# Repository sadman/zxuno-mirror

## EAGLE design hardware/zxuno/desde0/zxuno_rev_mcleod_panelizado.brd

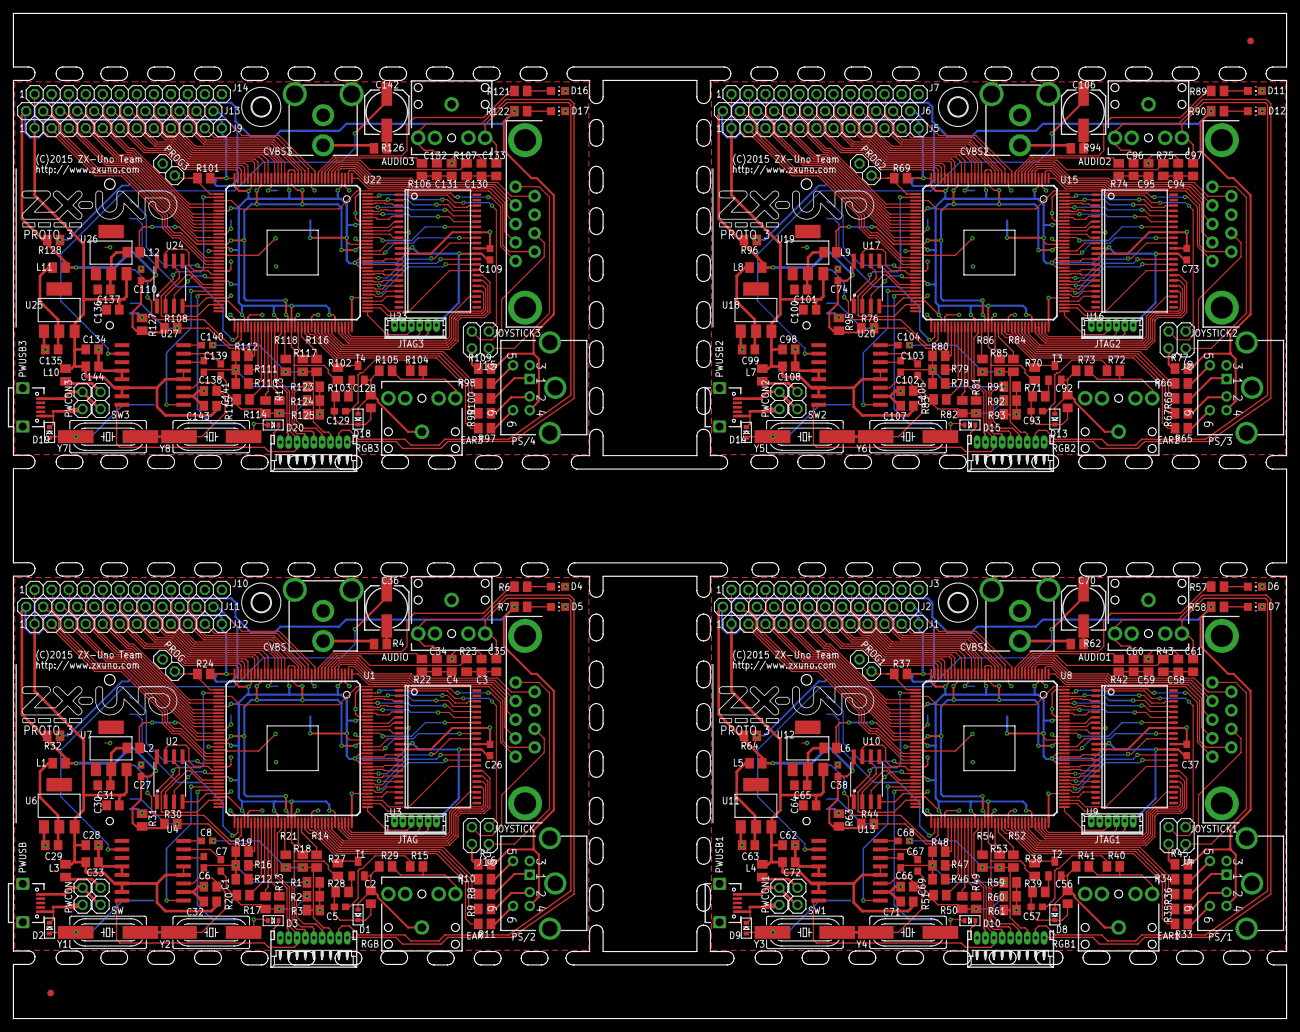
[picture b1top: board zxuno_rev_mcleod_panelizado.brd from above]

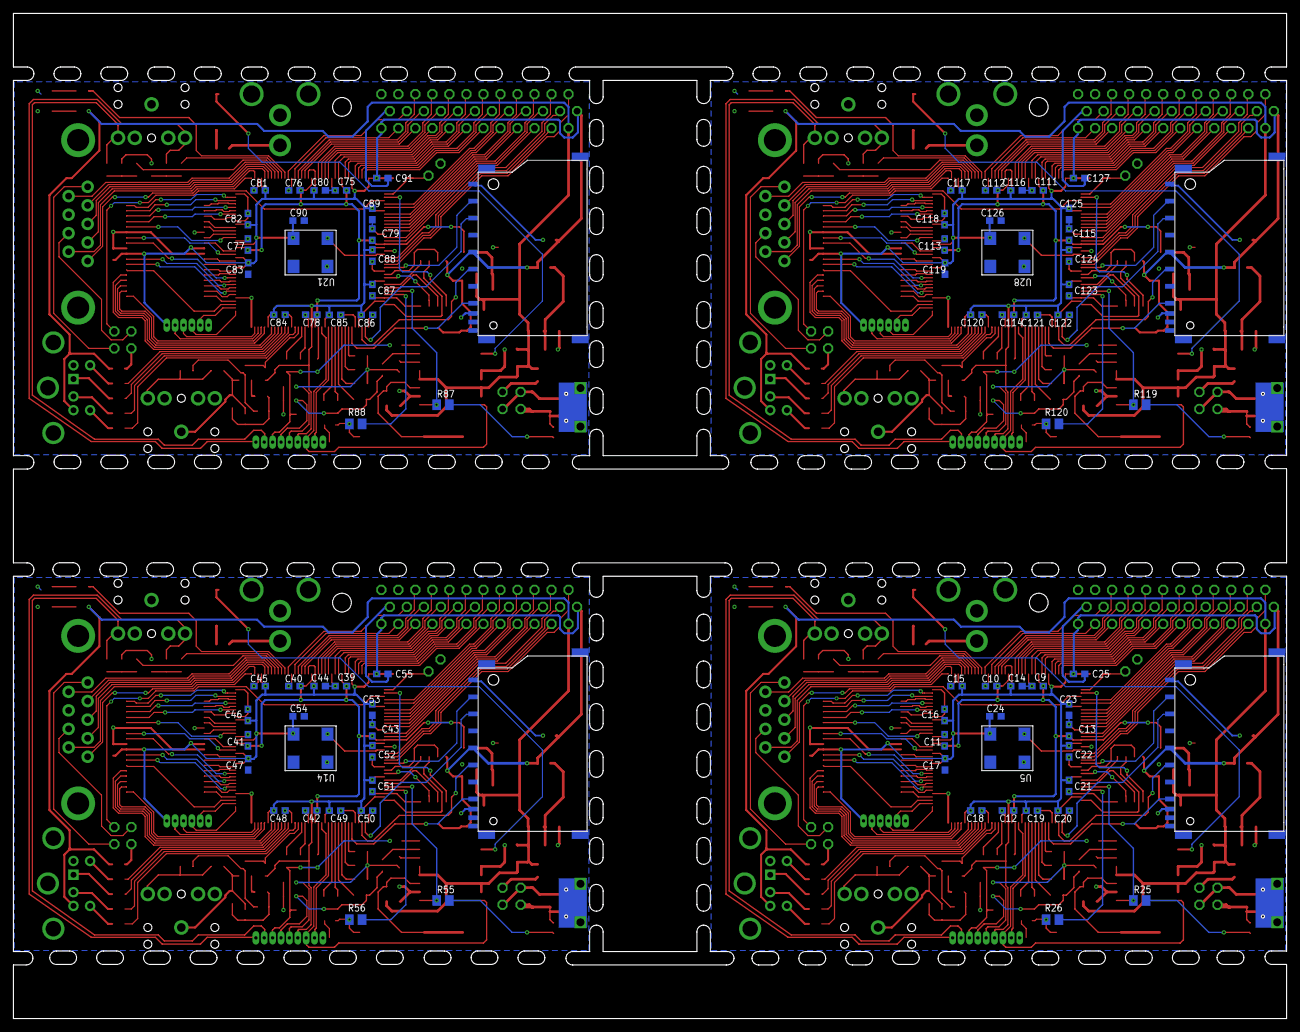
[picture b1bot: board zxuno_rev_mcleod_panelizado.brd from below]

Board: 2 copper layers, 190.0 x 150.0 mm, 414 parts (84 on the bottom side), 572 nets.

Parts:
AUDIO, AUDIO1, AUDIO2, AUDIO3: Audio; AUDIO-JACK
C1, C69, C105, C141: 7.5pF; C0805
C2, C3, C4, C56, C58, C59, C92, C94, C95, C128, C130, C131: 10nF; C0805
C5, C6, C7, C8, C9, C10, C11, C12, C13, C14, C15, C16, C17, C18, C19, C20, C21, C22, C23, C24, C25, C26, C27, C37, C38, C39, C40, C41, C42, C43, C44, C45, C46, C47, C48, C49, C50, C51, C52, C53, C54, C55, C57, C66, C67, C68, C73, C74, C75, C76, C77, C78, C79, C80, C81, C82, C83, C84, C85, C86, C87, C88, C89, C90, C91, C93, C102, C103, C104, C109, C110, C111, C112, C113, C114, C115, C116, C117, C118, C119, C120, C121, C122, C123, C124, C125, C126, C127, C129, C138, C139, C140: 100nF; C0603
C28, C29, C30, C31, C32, C33, C34, C35, C60, C61, C62, C63, C64, C65, C71, C72, C96, C97, C98, C99, C100, C101, C107, C108, C132, C133, C134, C135, C136, C137, C143, C144: 10uF; C0805
C36, C70, C106, C142: 220uF; 153CLV-0605
CVBS, CVBS1, CVBS2, CVBS3: RCA; RCA_JACK_RCJ-04X_-_DUPLICATE_1PRIMARY
D1, D2, D3, D8, D9, D10, D13, D14, D15, D18, D19, D20: SOD-523
D4, D5, D6, D7, D11, D12, D16, D17: CHIP-LED0805
E$1, E$2: FIDUCIAL_1MM
EAR, EAR1, EAR2, EAR3: EAR; AUDIO-JACK
H1, H2, H3, H4: MOUNT-HOLE2.8; 2,8
J1, J2, J3, J5, J6, J7, J9, J10, J11, J12, J13, J14: 1X12
J4, J8, J15, J16: 2X02
JOYSTICK, JOYSTICK1, JOYSTICK2, JOYSTICK3: DB9_MALE
JTAG, JTAG1, JTAG2, JTAG3: JTAG; 53047-06
L1, L2, L3, L4, L5, L6, L7, L8, L9, L10, L11, L12: M0805
PROG, PROG1, PROG2, PROG3: 1X02
PS/1, PS/2, PS/3, PS/4: PS/2 Keyb; DINC/MIN_TM/6_1PRIMARY
PWCON, PWCON1, PWCON2, PWCON3: 1X02
PWUSB, PWUSB1, PWUSB2, PWUSB3: MICROUSB; MICRO_USB_1PRIMARY
R1, R2, R3, R4, R59, R60, R61, R62, R91, R92, R93, R94, R123, R124, R125, R126: 75; M0805
R5, R6, R7, R8, R9, R10, R11, R12, R13, R14, R15, R33, R34, R35, R36, R40, R45, R46, R49, R52, R57, R58, R65, R66, R67, R68, R72, R77, R78, R81, R84, R89, R90, R97, R98, R99, R100, R104, R109, R110, R113, R116, R121, R122: 510; M0805
R16, R17, R18, R47, R50, R53, R79, R82, R85, R111, R114, R117: 1K; M0805
R19, R20, R21, R22, R23, R24, R37, R42, R43, R48, R51, R54, R69, R74, R75, R80, R83, R86, R101, R106, R107, R112, R115, R118: 2K; M0805
R25, R26, R27, R28, R29, R30, R31, R32, R38, R39, R41, R44, R55, R56, R63, R64, R70, R71, R73, R76, R87, R88, R95, R96, R102, R103, R105, R108, R119, R120, R127, R128: 10K; M0805
RGB, RGB1, RGB2, RGB3: RGB; 53048-09
SDCARD, SDCARD1, SDCARD2, SDCARD3: SDCMF-10915W010
SW, SW1, SW2, SW3: 1X02
T1, T2, T3, T4: BC846; SOT23
U1, U8, U15, U22: 6SLX9TQG144; TQ144
U2, U10, U17, U24: FLASH-SPI-25XXSMD1; SO08-EIAJ
U3, U9, U16, U23: TSOP44-II
U4, U13, U20, U27: AD724; SO16W
U5, U14, U21, U28: 50MHz; SM/OSC_1PRIMARY
U6, U11, U18, U25: 3.3V; SOT223
U7, U12, U19, U26: 1.2V; SOT223
Y1, Y3, Y5, Y7: 3.58M; HC49UP
Y2, Y4, Y6, Y8: 4.43M; HC49UP

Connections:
1.2V: C9.2, C10.2, C11.2, C12.2, C13.2, L2.2, U1.P19, U1.P28, U1.P52, U1.P89, U1.P128
1.2V1: C39.2, C40.2, C41.2, C42.2, C43.2, L6.2, U8.P19, U8.P28, U8.P52, U8.P89, U8.P128
1.2V2: C75.2, C76.2, C77.2, C78.2, C79.2, L9.2, U15.P19, U15.P28, U15.P52, U15.P89, U15.P128
1.2V3: C111.2, C112.2, C113.2, C114.2, C115.2, L12.2, U22.P19, U22.P28, U22.P52, U22.P89, U22.P128
3.3V: C14.2, C15.2, C16.2, C17.2, C18.2, C19.2, C20.2, C21.2, C22.2, C23.2, C24.2, C25.2, C26.1, C27.2, J11.1, J12.12, JTAG.1, L1.2, R24.2, R27.2, R30.1, R31.2, R32.2, RGB.4, SDCARD.4, U1.P4, U1.P18, U1.P20, U1.P31, U1.P36, U1.P42, U1.P53, U1.P63, U1.P69, U1.P76, U1.P86, U1.P90, U1.P103, U1.P122, U1.P125, U1.P129, U1.P135, U2.8, U3.11, U3.33, U5.4
3.3V1: C37.1, C38.2, C44.2, C45.2, C46.2, C47.2, C48.2, C49.2, C50.2, C51.2, C52.2, C53.2, C54.2, C55.2, J1.12, J2.1, JTAG1.1, L5.2, R37.2, R38.2, R44.1, R63.2, R64.2, RGB1.4, SDCARD1.4, U8.P4, U8.P18, U8.P20, U8.P31, U8.P36, U8.P42, U8.P53, U8.P63, U8.P69, U8.P76, U8.P86, U8.P90, U8.P103, U8.P122, U8.P125, U8.P129, U8.P135, U9.11, U9.33, U10.8, U14.4
3.3V2: C73.1, C74.2, C80.2, C81.2, C82.2, C83.2, C84.2, C85.2, C86.2, C87.2, C88.2, C89.2, C90.2, C91.2, J5.12, J6.1, JTAG2.1, L8.2, R69.2, R70.2, R76.1, R95.2, R96.2, RGB2.4, SDCARD2.4, U15.P4, U15.P18, U15.P20, U15.P31, U15.P36, U15.P42, U15.P53, U15.P63, U15.P69, U15.P76, U15.P86, U15.P90, U15.P103, U15.P122, U15.P125, U15.P129, U15.P135, U16.11, U16.33, U17.8, U21.4
3.3V3: C109.1, C110.2, C116.2, C117.2, C118.2, C119.2, C120.2, C121.2, C122.2, C123.2, C124.2, C125.2, C126.2, C127.2, J9.12, J13.1, JTAG3.1, L11.2, R101.2, R102.2, R108.1, R127.2, R128.2, RGB3.4, SDCARD3.4, U22.P4, U22.P18, U22.P20, U22.P31, U22.P36, U22.P42, U22.P53, U22.P63, U22.P69, U22.P76, U22.P86, U22.P90, U22.P103, U22.P122, U22.P125, U22.P129, U22.P135, U23.11, U23.33, U24.8, U28.4
5V: C28.1, C30.1, C32.2, C33.2, J12.1, L3.2, PS/2.4, R5.1, R7.2, U4.4, U4.5, U4.14, U4.15, U6.3, U7.3
5V1: C62.1, C64.1, C71.2, C72.2, J1.1, L4.2, PS/1.4, R45.1, R58.2, U11.3, U12.3, U13.4, U13.5, U13.14, U13.15
5V2: C98.1, C100.1, C107.2, C108.2, J5.1, L7.2, PS/3.4, R77.1, R90.2, U18.3, U19.3, U20.4, U20.5, U20.14, U20.15
5V3: C134.1, C136.1, C143.2, C144.2, J9.1, L10.2, PS/4.4, R109.1, R122.2, U25.3, U26.3, U27.4, U27.5, U27.14, U27.15
AUDIO_LEFT: R22.2, U1.P10
AUDIO_LEFT1: R42.2, U8.P10
AUDIO_LEFT2: R74.2, U15.P10
AUDIO_LEFT3: R106.2, U22.P10
AUDIO_RIGHT: R23.2, U1.P9
AUDIO_RIGHT1: R43.2, U8.P9
AUDIO_RIGHT2: R75.2, U15.P9
AUDIO_RIGHT3: R107.2, U22.P9
B: C6.2, R1.1, R12.1, R16.1, R19.1, RGB.5
B0: R19.2, U1.P79
B1: R16.2, U1.P80
B2: R12.2, U1.P81
B3: R48.2, U8.P79
B4: R47.2, U8.P80
B5: R46.2, U8.P81
B6: C66.2, R46.1, R47.1, R48.1, R59.1, RGB1.5
B7: R80.2, U15.P79
B8: R79.2, U15.P80
B9: R78.2, U15.P81
B10: C102.2, R78.1, R79.1, R80.1, R91.1, RGB2.5
B11: R112.2, U22.P79
B12: R111.2, U22.P80
B13: R110.2, U22.P81
B14: C138.2, R110.1, R111.1, R112.1, R123.1, RGB3.5
CLK: U1.P55, U5.3
CLK1: U8.P55, U14.3
CLK2: U15.P55, U21.3
CLK3: U22.P55, U28.3
CSYNC: RGB.3, U1.P87, U4.16
CSYNC1: RGB1.3, U8.P87, U13.16
CSYNC2: RGB2.3, U15.P87, U20.16
CSYNC3: RGB3.3, U22.P87, U27.16
EAR: R27.1, T1.3, U1.P94
EAR1: R38.1, T2.3, U8.P94
EAR2: R70.1, T3.3, U15.P94
EAR3: R102.1, T4.3, U22.P94
EXT1: J1.2, U8.P57
EXT2: J2.2, U8.P56
EXT3: J3.2, U8.P51
EXT4: J1.3, U8.P50
EXT5: J2.3, U8.P48
EXT6: J10.1, U1.P58
EXT7: J12.2, U1.P57
EXT8: J11.2, U1.P56
EXT9: J10.2, U1.P51
EXT10: J12.3, U1.P50
EXT11: J11.3, U1.P48
EXT12: J10.3, U1.P47
EXT13: J12.4, U1.P46
EXT14: J11.4, U1.P45
EXT15: J10.4, U1.P44
EXT16: J12.5, U1.P43
EXT17: J11.5, U1.P41
EXT18: J10.5, U1.P40
EXT19: J12.6, U1.P35
EXT20: J11.6, U1.P34
EXT21: J10.6, U1.P33
EXT22: J12.7, U1.P32
EXT23: J11.7, U1.P30
EXT24: J10.7, U1.P29
EXT25: J12.8, U1.P27
EXT26: J11.8, U1.P26
EXT27: J10.8, U1.P24
EXT28: J12.9, U1.P23
EXT29: J11.9, U1.P22
EXT30: J10.9, U1.P21
EXT31: J12.10, U1.P17
EXT32: J11.10, U1.P16
EXT33: J10.10, U1.P15
EXT34: J12.11, U1.P14
EXT35: J11.11, U1.P12
EXT36: J3.3, U8.P47
EXT37: J1.4, U8.P46
EXT38: J2.4, U8.P45
EXT39: J3.4, U8.P44
EXT40: J1.5, U8.P43
EXT41: J2.5, U8.P41
EXT42: J3.5, U8.P40
EXT43: J1.6, U8.P35
EXT44: J2.6, U8.P34
EXT45: J3.6, U8.P33
EXT46: J1.7, U8.P32
EXT47: J2.7, U8.P30
EXT48: J3.7, U8.P29
EXT49: J1.8, U8.P27
EXT50: J2.8, U8.P26
EXT51: J3.8, U8.P24
EXT52: J1.9, U8.P23
EXT53: J2.9, U8.P22
EXT54: J3.9, U8.P21
EXT55: J1.10, U8.P17
EXT56: J2.10, U8.P16
EXT57: J3.10, U8.P15
EXT58: J1.11, U8.P14
EXT59: J2.11, U8.P12
EXT60: J3.1, U8.P58
EXT61: J5.2, U15.P57
EXT62: J6.2, U15.P56
EXT63: J7.2, U15.P51
EXT64: J5.3, U15.P50
EXT65: J6.3, U15.P48
EXT66: J7.3, U15.P47
EXT67: J5.4, U15.P46
EXT68: J6.4, U15.P45
EXT69: J7.4, U15.P44
EXT70: J5.5, U15.P43
EXT71: J6.5, U15.P41
EXT72: J7.5, U15.P40
EXT73: J5.6, U15.P35
EXT74: J6.6, U15.P34
EXT75: J7.6, U15.P33
EXT76: J5.7, U15.P32
EXT77: J6.7, U15.P30
EXT78: J7.7, U15.P29
EXT79: J5.8, U15.P27
EXT80: J6.8, U15.P26
EXT81: J7.8, U15.P24
EXT82: J5.9, U15.P23
EXT83: J6.9, U15.P22
EXT84: J7.9, U15.P21
EXT85: J5.10, U15.P17
EXT86: J6.10, U15.P16
EXT87: J7.10, U15.P15
EXT88: J5.11, U15.P14
EXT89: J6.11, U15.P12
EXT90: J7.1, U15.P58
EXT91: J9.2, U22.P57
EXT92: J13.2, U22.P56
EXT93: J14.2, U22.P51
EXT94: J9.3, U22.P50
EXT95: J13.3, U22.P48
EXT96: J14.3, U22.P47
EXT97: J9.4, U22.P46
EXT98: J13.4, U22.P45
EXT99: J14.4, U22.P44
EXT100: J9.5, U22.P43
EXT101: J13.5, U22.P41
EXT102: J14.5, U22.P40
EXT103: J9.6, U22.P35
EXT104: J13.6, U22.P34
EXT105: J14.6, U22.P33
EXT106: J9.7, U22.P32
EXT107: J13.7, U22.P30
EXT108: J14.7, U22.P29
EXT109: J9.8, U22.P27
EXT110: J13.8, U22.P26
EXT111: J14.8, U22.P24
EXT112: J9.9, U22.P23
EXT113: J13.9, U22.P22
EXT114: J14.9, U22.P21
EXT115: J9.10, U22.P17
EXT116: J13.10, U22.P16
EXT117: J14.10, U22.P15
EXT118: J9.11, U22.P14
EXT119: J13.11, U22.P12
EXT120: J14.1, U22.P58
FLASH_CS: U1.P38, U2.1
FLASH_CS1: U8.P38, U10.1
FLASH_CS2: U15.P38, U17.1
FLASH_CS3: U22.P38, U24.1
FLASH_HOLD: U1.P61, U2.7
FLASH_HOLD1: U8.P61, U10.7
FLASH_HOLD2: U15.P61, U17.7
FLASH_HOLD3: U22.P61, U24.7
FLASH_MISO: U1.P65, U2.2
FLASH_MISO1: U8.P65, U10.2
FLASH_MISO2: U15.P65, U17.2
FLASH_MISO3: U22.P65, U24.2
FLASH_MOSI: U1.P64, U2.5
FLASH_MOSI1: U8.P64, U10.5
FLASH_MOSI2: U15.P64, U17.5
FLASH_MOSI3: U22.P64, U24.5
FLASH_SCK: U1.P70, U2.6
FLASH_SCK1: U8.P70, U10.6
FLASH_SCK2: U15.P70, U17.6
FLASH_SCK3: U22.P70, U24.6
FLASH_WP: U1.P62, U2.3
FLASH_WP1: U8.P62, U10.3
FLASH_WP2: U15.P62, U17.3
FLASH_WP3: U22.P62, U24.3
G: C7.2, R2.1, R13.1, R17.1, R20.1, RGB.6
G0: R20.2, U1.P82
G1: R17.2, U1.P83
G2: R13.2, U1.P84
G3: R51.2, U8.P82
G4: R50.2, U8.P83
G5: R49.2, U8.P84
G6: C67.2, R49.1, R50.1, R51.1, R60.1, RGB1.6
G7: R83.2, U15.P82
G8: R82.2, U15.P83
G9: R81.2, U15.P84
G10: C103.2, R81.1, R82.1, R83.1, R92.1, RGB2.6
G11: R115.2, U22.P82
G12: R114.2, U22.P83
G13: R113.2, U22.P84
G14: C139.2, R113.1, R114.1, R115.1, R124.1, RGB3.6
GND: AUDIO.SLEEVE, C1.2, C2.2, C3.2, C4.2, C9.1, C10.1, C11.1, C12.1, C13.1, C14.1, C15.1, C16.1, C17.1, C18.1, C19.1, C20.1, C21.1, C22.1, C23.1, C24.1, C25.1, C26.2, C27.1, C28.2, C29.2, C30.2, C31.2, C32.1, C33.1, CVBS.4, D1.A, D2.K, D3.K, D4.C, D5.C, EAR.SLEEVE, J10.12, J11.12, JOYSTICK.8, JTAG.6, PROG.1, PS/2.3, PWCON.1, PWUSB.5, R1.2, R2.2, R3.2, R29.2, RGB.1, SDCARD.3, SDCARD.6, SDCARD.M1, SDCARD.M2, SDCARD.M3, SDCARD.M4, T1.2, U1.P3, U1.P13, U1.P25, U1.P49, U1.P54, U1.P60, U1.P68, U1.P73, U1.P77, U1.P91, U1.P96, U1.P108, U1.P113, U1.P130, U1.P136, U1.P144, U2.4, U3.8, U3.12, U3.34, U3.37, U4.2, U4.12, U4.13, U5.2, U6.1, U7.1
GND1: AUDIO1.SLEEVE, C37.2, C38.1, C39.1, C40.1, C41.1, C42.1, C43.1, C44.1, C45.1, C46.1, C47.1, C48.1, C49.1, C50.1, C51.1, C52.1, C53.1, C54.1, C55.1, C56.2, C58.2, C59.2, C62.2, C63.2, C64.2, C65.2, C69.2, C71.1, C72.1, CVBS1.4, D6.C, D7.C, D8.A, D9.K, D10.K, EAR1.SLEEVE, J2.12, J3.12, JOYSTICK1.8, JTAG1.6, PROG1.1, PS/1.3, PWCON1.1, PWUSB1.5, R41.2, R59.2, R60.2, R61.2, RGB1.1, SDCARD1.3, SDCARD1.6, SDCARD1.M1, SDCARD1.M2, SDCARD1.M3, SDCARD1.M4, T2.2, U8.P3, U8.P13, U8.P25, U8.P49, U8.P54, U8.P60, U8.P68, U8.P73, U8.P77, U8.P91, U8.P96, U8.P108, U8.P113, U8.P130, U8.P136, U8.P144, U9.8, U9.12, U9.34, U9.37, U10.4, U11.1, U12.1, U13.2, U13.12, U13.13, U14.2
GND2: AUDIO2.SLEEVE, C73.2, C74.1, C75.1, C76.1, C77.1, C78.1, C79.1, C80.1, C81.1, C82.1, C83.1, C84.1, C85.1, C86.1, C87.1, C88.1, C89.1, C90.1, C91.1, C92.2, C94.2, C95.2, C98.2, C99.2, C100.2, C101.2, C105.2, C107.1, C108.1, CVBS2.4, D11.C, D12.C, D13.A, D14.K, D15.K, EAR2.SLEEVE, J6.12, J7.12, JOYSTICK2.8, JTAG2.6, PROG2.1, PS/3.3, PWCON2.1, PWUSB2.5, R73.2, R91.2, R92.2, R93.2, RGB2.1, SDCARD2.3, SDCARD2.6, SDCARD2.M1, SDCARD2.M2, SDCARD2.M3, SDCARD2.M4, T3.2, U15.P3, U15.P13, U15.P25, U15.P49, U15.P54, U15.P60, U15.P68, U15.P73, U15.P77, U15.P91, U15.P96, U15.P108, U15.P113, U15.P130, U15.P136, U15.P144, U16.8, U16.12, U16.34, U16.37, U17.4, U18.1, U19.1, U20.2, U20.12, U20.13, U21.2
GND3: AUDIO3.SLEEVE, C109.2, C110.1, C111.1, C112.1, C113.1, C114.1, C115.1, C116.1, C117.1, C118.1, C119.1, C120.1, C121.1, C122.1, C123.1, C124.1, C125.1, C126.1, C127.1, C128.2, C130.2, C131.2, C134.2, C135.2, C136.2, C137.2, C141.2, C143.1, C144.1, CVBS3.4, D16.C, D17.C, D18.A, D19.K, D20.K, EAR3.SLEEVE, J13.12, J14.12, JOYSTICK3.8, JTAG3.6, PROG3.1, PS/4.3, PWCON3.1, PWUSB3.5, R105.2, R123.2, R124.2, R125.2, RGB3.1, SDCARD3.3, SDCARD3.6, SDCARD3.M1, SDCARD3.M2, SDCARD3.M3, SDCARD3.M4, T4.2, U22.P3, U22.P13, U22.P25, U22.P49, U22.P54, U22.P60, U22.P68, U22.P73, U22.P77, U22.P91, U22.P96, U22.P108, U22.P113, U22.P130, U22.P136, U22.P144, U23.8, U23.12, U23.34, U23.37, U24.4, U25.1, U26.1, U27.2, U27.12, U27.13, U28.2
JOY_DOWN: JOYSTICK.2, U1.P5
JOY_DOWN1: JOYSTICK1.2, U8.P5
JOY_DOWN2: JOYSTICK2.2, U15.P5
JOY_DOWN3: JOYSTICK3.2, U22.P5
JOY_FIRE1: JOYSTICK.6, U1.P2
JOY_FIRE2: JOYSTICK.9, U1.P8
JOY_FIRE3: J16.1, U1.P39
JOY_FIRE4: JOYSTICK1.6, U8.P2
JOY_FIRE5: JOYSTICK1.9, U8.P8
JOY_FIRE6: J4.1, U8.P39
JOY_FIRE7: JOYSTICK2.6, U15.P2
JOY_FIRE8: JOYSTICK2.9, U15.P8
JOY_FIRE9: J8.1, U15.P39
JOY_FIRE10: JOYSTICK3.6, U22.P2
JOY_FIRE11: JOYSTICK3.9, U22.P8
JOY_FIRE12: J15.1, U22.P39
JOY_LEFT: JOYSTICK.3, U1.P6
JOY_LEFT1: JOYSTICK1.3, U8.P6
JOY_LEFT2: JOYSTICK2.3, U15.P6
JOY_LEFT3: JOYSTICK3.3, U22.P6
JOY_RIGHT: JOYSTICK.4, U1.P7
JOY_RIGHT1: JOYSTICK1.4, U8.P7
JOY_RIGHT2: JOYSTICK2.4, U15.P7
JOY_RIGHT3: JOYSTICK3.4, U22.P7
JOY_UP: JOYSTICK.1, U1.P1
JOY_UP1: JOYSTICK1.1, U8.P1
JOY_UP2: JOYSTICK2.1, U15.P1
JOY_UP3: JOYSTICK3.1, U22.P1
L-OUT: AUDIO.TIP, C34.2, RGB.9
L-OUT1: AUDIO1.TIP, C60.2, RGB1.9
L-OUT2: AUDIO2.TIP, C96.2, RGB2.9
L-OUT3: AUDIO3.TIP, C132.2, RGB3.9
LED: R6.2, U1.P11
LED1: R57.2, U8.P11
LED2: R89.2, U15.P11
LED3: R121.2, U22.P11
unnamed: PS/2.6, R11.1
unnamed: PS/2.5, R10.1
unnamed: PS/2.2, R9.1
unnamed: PS/2.1, R8.1
unnamed: PROG.2, R24.1, U1.P37
unnamed: R28.2, T1.1
unnamed: C2.1, C5.1, D1.K, R28.1
unnamed: C5.2, R15.2
unnamed: EAR.TIP, R15.1, R29.1
unnamed: C3.1, C35.1, R23.1
unnamed: C4.1, C34.1, R22.1
unnamed: PWCON.2, PWUSB.1, SW.2
unnamed: L3.1, SW.1
unnamed: C29.1, L1.1, U6.2
unnamed: J16.4, R5.2
unnamed: PS/1.6, R33.1
unnamed: C31.1, L2.1, U7.2
unnamed: R31.1, SDCARD.8
unnamed: C8.1, U4.8
unnamed: R32.1, SDCARD.9
unnamed: C7.1, U4.7
unnamed: C6.1, U4.6
unnamed: C1.1, U4.3, Y1.2, Y2.2
unnamed: D3.A, R26.1, Y2.1
unnamed: D2.A, R25.2, Y1.1
unnamed: C36.+, U4.10
unnamed: C36.-, R4.1
unnamed: CVBS.3, R4.2
unnamed: PS/1.5, R34.1
unnamed: PS/1.2, R35.1
unnamed: D4.A, R6.1
unnamed: D5.A, R7.1
unnamed: PS/1.1, R36.1
unnamed: R39.2, T2.1
unnamed: C56.1, C57.1, D8.K, R39.1
unnamed: C57.2, R40.2
unnamed: EAR1.TIP, R40.1, R41.1
unnamed: C58.1, C61.1, R43.1
unnamed: C59.1, C60.1, R42.1
unnamed: PWCON1.2, PWUSB1.1, SW1.2
unnamed: L4.1, SW1.1
unnamed: C63.1, L5.1, U11.2
unnamed: C65.1, L6.1, U12.2
unnamed: C67.1, U13.7
unnamed: C66.1, U13.6
unnamed: C69.1, U13.3, Y3.2, Y4.2
unnamed: D10.A, R56.1, Y4.1
unnamed: D9.A, R55.2, Y3.1
unnamed: C70.+, U13.10
unnamed: C68.1, U13.8
unnamed: C70.-, R62.1
unnamed: CVBS1.3, R62.2
unnamed: D6.A, R57.1
unnamed: D7.A, R58.1
unnamed: PROG1.2, R37.1, U8.P37
unnamed: R63.1, SDCARD1.8
unnamed: R64.1, SDCARD1.9
unnamed: J4.4, R45.2
unnamed: PS/3.6, R65.1
unnamed: PS/3.5, R66.1
unnamed: PS/3.2, R67.1
unnamed: PS/3.1, R68.1
unnamed: R71.2, T3.1
unnamed: C92.1, C93.1, D13.K, R71.1
unnamed: C93.2, R72.2
unnamed: EAR2.TIP, R72.1, R73.1
unnamed: C94.1, C97.1, R75.1
unnamed: C95.1, C96.1, R74.1
unnamed: PWCON2.2, PWUSB2.1, SW2.2
unnamed: L7.1, SW2.1
unnamed: C99.1, L8.1, U18.2
unnamed: C101.1, L9.1, U19.2
unnamed: C103.1, U20.7
unnamed: C102.1, U20.6
unnamed: C105.1, U20.3, Y5.2, Y6.2
unnamed: D15.A, R88.1, Y6.1
unnamed: D14.A, R87.2, Y5.1
unnamed: C106.+, U20.10
unnamed: C104.1, U20.8
unnamed: C106.-, R94.1
unnamed: CVBS2.3, R94.2
unnamed: D11.A, R89.1
unnamed: D12.A, R90.1
unnamed: PROG2.2, R69.1, U15.P37
unnamed: R95.1, SDCARD2.8
unnamed: R96.1, SDCARD2.9
unnamed: J8.4, R77.2
unnamed: PS/4.6, R97.1
unnamed: PS/4.5, R98.1
unnamed: PS/4.2, R99.1
unnamed: PS/4.1, R100.1
unnamed: R103.2, T4.1
unnamed: C128.1, C129.1, D18.K, R103.1
unnamed: C129.2, R104.2
unnamed: EAR3.TIP, R104.1, R105.1
unnamed: C130.1, C133.1, R107.1
unnamed: C131.1, C132.1, R106.1
unnamed: PWCON3.2, PWUSB3.1, SW3.2
unnamed: L10.1, SW3.1
unnamed: C135.1, L11.1, U25.2
unnamed: C137.1, L12.1, U26.2
unnamed: C139.1, U27.7
unnamed: C138.1, U27.6
unnamed: C141.1, U27.3, Y7.2, Y8.2
unnamed: D20.A, R120.1, Y8.1
unnamed: D19.A, R119.2, Y7.1
unnamed: C142.+, U27.10
unnamed: C140.1, U27.8
unnamed: C142.-, R126.1
unnamed: CVBS3.3, R126.2
unnamed: D16.A, R121.1
unnamed: D17.A, R122.1
unnamed: PROG3.2, R101.1, U22.P37
unnamed: R127.1, SDCARD3.8
unnamed: R128.1, SDCARD3.9
unnamed: J15.4, R109.2
PIN1: J4.3, JOYSTICK1.7
PIN2: J4.2, JOYSTICK1.5
PIN3: J8.3, JOYSTICK2.7
PIN4: J8.2, JOYSTICK2.5
PIN5: J16.2, JOYSTICK.5
PIN6: J15.3, JOYSTICK3.7
PIN7: J16.3, JOYSTICK.7
PIN8: J15.2, JOYSTICK3.5
PS2_CLK: R10.2, U1.P99
PS2_CLK1: R34.2, U8.P99
PS2_CLK2: R66.2, U15.P99
PS2_CLK3: R98.2, U22.P99
PS2_DATA: R8.2, U1.P98
PS2_DATA1: R36.2, U8.P98
PS2_DATA2: R68.2, U15.P98
PS2_DATA3: R100.2, U22.P98
PS2_PIN1: R33.2, U8.P95
PS2_PIN2: R9.2, U1.P97
PS2_PIN3: R35.2, U8.P97
PS2_PIN4: R65.2, U15.P95
PS2_PIN5: R67.2, U15.P97
PS2_PIN6: R11.2, U1.P95
PS2_PIN7: R97.2, U22.P95
PS2_PIN8: R99.2, U22.P97
R: C8.2, R3.1, R14.1, R18.1, R21.1, RGB.7
R0: R21.2, U1.P88
R1: R18.2, U1.P92
R2: R14.2, U1.P93
R3: R54.2, U8.P88
R4: R53.2, U8.P92
R5: R52.2, U8.P93
R6: C68.2, R52.1, R53.1, R54.1, R61.1, RGB1.7
R7: R86.2, U15.P88
R8: R85.2, U15.P92
R9: R84.2, U15.P93
R10: C104.2, R84.1, R85.1, R86.1, R93.1, RGB2.7
R11: R118.2, U22.P88
R12: R117.2, U22.P92
R13: R116.2, U22.P93
R14: C140.2, R116.1, R117.1, R118.1, R125.1, RGB3.7
R-OUT: AUDIO.RING, C35.2, RGB.8
R-OUT1: AUDIO1.RING, C61.2, RGB1.8
R-OUT2: AUDIO2.RING, C97.2, RGB2.8
R-OUT3: AUDIO3.RING, C133.2, RGB3.8
SD_CS: SDCARD.1, U1.P59
SD_CS1: SDCARD1.1, U8.P59
SD_CS2: SDCARD2.1, U15.P59
SD_CS3: SDCARD3.1, U22.P59
SD_MISO: R30.2, SDCARD.7, U1.P78
SD_MISO1: R44.2, SDCARD1.7, U8.P78
SD_MISO2: R76.2, SDCARD2.7, U15.P78
SD_MISO3: R108.2, SDCARD3.7, U22.P78
SD_MOSI: SDCARD.2, U1.P74
SD_MOSI1: SDCARD1.2, U8.P74
SD_MOSI2: SDCARD2.2, U15.P74
SD_MOSI3: SDCARD3.2, U22.P74
SD_SCK: SDCARD.5, U1.P75
SD_SCK1: SDCARD1.5, U8.P75
SD_SCK2: SDCARD2.5, U15.P75
SD_SCK3: SDCARD3.5, U22.P75
STDN: R25.1, U1.P66, U4.1
STDN1: R55.1, U8.P66, U13.1
STDN2: R87.1, U15.P66, U20.1
STDN3: R119.1, U22.P66, U27.1
STDNB: R26.2, U1.P67
STDNB1: R56.2, U8.P67
STDNB2: R88.2, U15.P67
STDNB3: R120.2, U22.P67
TCK: JTAG.4, U1.P109
TCK1: JTAG1.4, U8.P109
TCK2: JTAG2.4, U15.P109
TCK3: JTAG3.4, U22.P109
TDI: JTAG.5, U1.P110
TDI1: JTAG1.5, U8.P110
TDI2: JTAG2.5, U15.P110
TDI3: JTAG3.5, U22.P110
TDO: JTAG.2, U1.P106
TDO1: JTAG1.2, U8.P106
TDO2: JTAG2.2, U15.P106
TDO3: JTAG3.2, U22.P106
TMS: JTAG.3, U1.P107
TMS1: JTAG1.3, U8.P107
TMS2: JTAG2.3, U15.P107
TMS3: JTAG3.3, U22.P107
VSYNC: RGB.2, U1.P85
VSYNC1: RGB1.2, U8.P85
VSYNC2: RGB2.2, U15.P85
VSYNC3: RGB3.2, U22.P85
WR: U1.P121, U3.15
WR1: U8.P121, U9.15
WR2: U15.P121, U16.15
WR3: U22.P121, U23.15
XA0: U1.P141, U3.3
XA1: U1.P139, U3.4
XA2: U1.P137, U3.5
XA3: U1.P134, U3.6
XA4: U1.P133, U3.7
XA5: U1.P120, U3.16
XA6: U1.P118, U3.17
XA7: U1.P116, U3.18
XA8: U1.P114, U3.19
XA9: U1.P112, U3.20
XA10: U1.P104, U3.26
XA11: U1.P102, U3.27
XA12: U1.P101, U3.28
XA13: U1.P100, U3.29
XA14: U1.P111, U3.30
XA15: U1.P131, U3.38
XA16: U1.P138, U3.39
XA17: U1.P140, U3.40
XA18: U1.P142, U3.41
XA19: U1.P105, U3.25
XA20: U1.P143, U3.42
XA21: U8.P141, U9.3
XA22: U8.P137, U9.5
XA23: U8.P134, U9.6
XA24: U8.P133, U9.7
XA25: U8.P120, U9.16
XA26: U8.P118, U9.17
XA27: U8.P116, U9.18
XA28: U8.P114, U9.19
XA29: U8.P112, U9.20
XA30: U8.P104, U9.26
XA31: U8.P102, U9.27
XA32: U8.P101, U9.28
XA33: U8.P100, U9.29
XA34: U8.P111, U9.30
XA35: U8.P131, U9.38
XA36: U8.P138, U9.39
XA37: U8.P140, U9.40
XA38: U8.P142, U9.41
XA39: U8.P105, U9.25
XA40: U8.P143, U9.42
XA41: U8.P139, U9.4
XA42: U15.P141, U16.3
XA43: U15.P137, U16.5
XA44: U15.P134, U16.6
XA45: U15.P133, U16.7
XA46: U15.P120, U16.16
XA47: U15.P118, U16.17
XA48: U15.P116, U16.18
XA49: U15.P114, U16.19
XA50: U15.P112, U16.20
XA51: U15.P104, U16.26
XA52: U15.P102, U16.27
XA53: U15.P101, U16.28
XA54: U15.P100, U16.29
XA55: U15.P111, U16.30
XA56: U15.P131, U16.38
XA57: U15.P138, U16.39
XA58: U15.P140, U16.40
XA59: U15.P142, U16.41
XA60: U15.P105, U16.25
XA61: U15.P143, U16.42
XA62: U15.P139, U16.4
XA63: U22.P141, U23.3
XA64: U22.P137, U23.5
XA65: U22.P134, U23.6
XA66: U22.P133, U23.7
XA67: U22.P120, U23.16
XA68: U22.P118, U23.17
XA69: U22.P116, U23.18
XA70: U22.P114, U23.19
XA71: U22.P112, U23.20
XA72: U22.P104, U23.26
XA73: U22.P102, U23.27
XA74: U22.P101, U23.28
XA75: U22.P100, U23.29
XA76: U22.P111, U23.30
XA77: U22.P131, U23.38
XA78: U22.P138, U23.39
XA79: U22.P140, U23.40
XA80: U22.P142, U23.41
XA81: U22.P105, U23.25
XA82: U22.P143, U23.42
XA83: U22.P139, U23.4
XD0: U1.P132, U3.9
XD1: U1.P127, U3.10
XD2: U1.P124, U3.13
XD3: U1.P123, U3.14
XD4: U1.P115, U3.31
XD5: U1.P117, U3.32
XD6: U1.P119, U3.35
XD7: U1.P126, U3.36
XD8: U8.P132, U9.9
XD9: U8.P127, U9.10
XD10: U8.P124, U9.13
XD11: U8.P123, U9.14
XD12: U8.P115, U9.31
XD13: U8.P117, U9.32
XD14: U8.P119, U9.35
XD15: U8.P126, U9.36
XD16: U15.P132, U16.9
XD17: U15.P127, U16.10
XD18: U15.P124, U16.13
XD19: U15.P123, U16.14
XD20: U15.P115, U16.31
XD21: U15.P117, U16.32
XD22: U15.P119, U16.35
XD23: U15.P126, U16.36
XD24: U22.P132, U23.9
XD25: U22.P127, U23.10
XD26: U22.P124, U23.13
XD27: U22.P123, U23.14
XD28: U22.P115, U23.31
XD29: U22.P117, U23.32
XD30: U22.P119, U23.35
XD31: U22.P126, U23.36

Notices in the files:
hardware/zxuno/desde0/zxuno_rev_mcleod_panelizado.brd:
(C)2015 ZX-Uno Team
parts and their libraries:
SparkFun-Connectors: Licensing: Creative Commons ShareAlike 4.0 International - https://creativecommons.org/licenses/by-sa/4.0
